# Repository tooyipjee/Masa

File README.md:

**Masa: A Smart, Energy-Efficient Retro Clock**
=====================================================
**Introduction**
---------------
Masa, the Malaysian word for time, is a project that brings together modern electronic components to achieve a beautiful vintage look. Masa combines the aesthetic of traditional Nixie tubes with modern LED technology and advanced features.

**Project Overview**
--------------------
Masa is a type of electronic clock that replicates the vintage aesthetic of traditional Nixie clocks while using modern LED technology. It displays the time and can also display additional panels such as weather, tickers, and other illustrations. Masa has internet connectivity, allowing it to retrieve data from the internet and features several onboard environmental sensors.

**Key Features**
----------------
* LEDs with full brightness and color control
* Environmental sensor to measure room temperature and humidity
* Phototransistor for ambient light measurement
* ESP32-S2 to drive and interface with sensors and get the latest time from the NTP server over WiFi
* Compatible with rapidly prototype-able Cricut-based perspex "displays"
* Powered by USB-C

**Specification**
---------------
* Microcontroller: ESP32-S2
* WiFi: 802.11b/g/n
* FLASH: 4MB
* Programming: USB over UART
* Humidity and Temperature Sensor: SHT20
    + Capacitive type humidity sensor
    + Band gap temperature sensor
    + Digital processing unit - I2C
* Light Sensor: TEMT6000X01
    + High photo sensitivity
    + Adapted to human eye responsivity
    + Angle of half sensitivity ± 60°
* Power: USB-C + 3.3V LDO

**Acknowledgement**
----------------
Special thanks to JLCPCB for sponsoring this project. Their rapid prototyping and high-quality assembly services enabled us to bring this project to life.

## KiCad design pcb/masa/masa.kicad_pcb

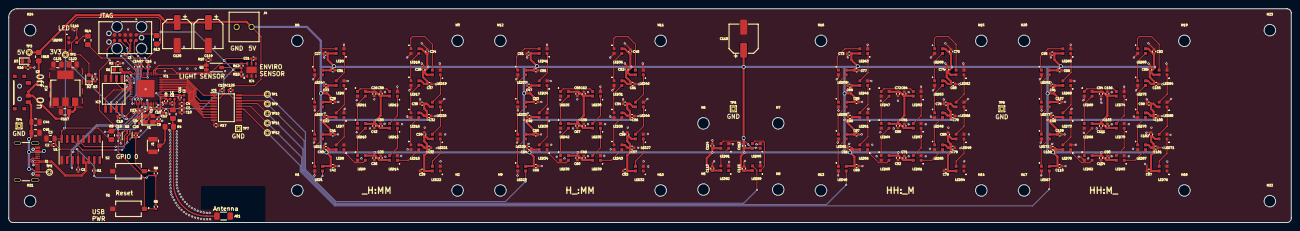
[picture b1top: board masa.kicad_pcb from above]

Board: 4 copper layers, 300.0 x 50.0 mm, 292 parts (0 on the bottom side), 144 nets.

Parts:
AE1: ANT3216LL00R2400A; R_1206_3216Metric_Pad1.30x1.75mm_HandSolder
C1, C2, C10, C13, C15, C16, C17, C18, C21, C22, C23, C24, C25, C26, C27, C28, C29, C30, C31, C32, C33, C34, C35, C36, C37, C38, C39, C40, C41, C42, C43, C46, C47, C48, C49, C50, C51, C52, C53, C54, C55, C56, C57, C58, C59, C60, C61, C62, C63, C64, C65, C66, C67, C68, C69, C70, C71, C72, C73, C74, C75, C76, C77, C78, C79, C80, C81, C82, C83, C84, C85, C86, C87, C88, C89, C90, C91, C92, C93, C94, C95, C96, C97, C98, C99, C100, C101, C102, C103, C104, C105, C106, C107, C108, C109, C110, C111, C112, C113, C114, C115, C116, C124, C125: 100n; C_0402_1005Metric
C3, C44, C45, C117, C121, C122: 10u; C_0805_2012Metric
C4, C12, C19, C20: 1u; C_0402_1005Metric
C5, C9: 20p; C_0402_1005Metric
C6: 4p; C_0402_1005Metric
C7, C11: 10u_0402; C_0402_1005Metric
C8: 5p; C_0402_1005Metric
C14: 100p; C_0402_1005Metric
C118, C119, C120: 100uF_E; CP_Elec_6.3x7.7
D1, D2, D3: Green_0603; LED_0603_1608Metric
H1, H2, H3, H4, H5, H6, H7, H8, H9, H10, H11, H12, H13, H14, H15, H16, H17, H18, H19, H20, H21, H22, H23, H24: MountingHole; MountingHole_2.7mm_M2.5
IC1: ESP32-S2FH4; QFN40P700X700X90-57N-D
IC2: AMS1117-3.3; SOT-223-3_TabPin2
IC3: W25Q64JVSSIQ; SOIC127P790X216-8N
IC4: SHT20; SON100P300X300X110-7N
IC5: TXS0108EPWR; SOP65P640X120-20N
J1: U.FL-R-SMT-1_10_
J2: GT-USB-7010; GT-USB-7010A
J3: TC2050-IDC
J4: KF350-3.5-2P; KF350352P
L1, L2: 1.8nH; L_0402_1005Metric
LED1, LED2, LED3, LED4, LED5, LED6, LED7, LED8, LED9, LED10, LED11, LED12, LED13, LED14, LED15, LED16, LED17, LED18, LED19, LED20, LED21, LED22, LED23, LED24, LED25, LED26, LED27, LED28, LED29, LED30, LED31, LED32, LED33, LED34, LED35, LED36, LED37, LED38, LED39, LED40, LED41, LED42, LED43, LED44, LED45, LED46, LED47, LED48, LED49, LED50, LED51, LED52, LED53, LED54, LED55, LED56, LED57, LED58, LED59, LED60, LED61, LED62, LED63, LED64, LED65, LED66, LED67, LED68, LED69, LED70, LED71, LED72, LED73, LED74, LED75, LED76, LED77, LED78, LED79, LED80, LED81, LED82, LED83, LED84, LED85, LED86, LED87, LED88, LED89, LED90, LED91, LED92, LED93: WS2812B-2020; WS2812B2020
Q1: MUN5214DW1T1G; SOT-363_SC-70-6
Q2: TEMT6000X01
R1: DNF_0402; R_0402_1005Metric
R2, R3: 1k; R_0402_1005Metric
R4, R9, R13: DNF_0805; R_0805_2012Metric_Pad1.20x1.40mm_HandSolder
R5, R14, R15: 0; R_0805_2012Metric_Pad1.20x1.40mm_HandSolder
R6, R7, R8, R10, R17: 10k; R_0402_1005Metric
R11, R12: 4.7k; R_0402_1005Metric
R16: 2.2k; R_0402_1005Metric
S1, S2: TS-1101-C-W; TS1101CW
S3: K3-1296S-E1; K31296SE1
TP1, TP2, TP3, TP5, TP9, TP10, TP11, TP12: TestPoint; TestPoint_THTPad_D1.0mm_Drill0.5mm
TP4, TP6, TP7, TP8: TestPoint; TestPoint_THTPad_1.0x1.0mm_Drill0.5mm
U1: CH340C; SOIC-16_3.9x9.9mm_P1.27mm
Y1: SX25Y040000BF1T-C; Crystal_SMD_2520-4Pin_2.5x2.0mm

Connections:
+3V3: C1.1, C2.1, C3.1, C4.1, C7.1, C10.1, C12.1, C13.1, C14.1, C15.1, C16.1, C17.1, C21.1, C116.1, C121.1, C122.1, C124.1, D2.2 (A), IC1.1 (VDDA_1), IC1.20 (VDD3P3_RTC), IC1.27 (VDD3P3_RTC_IO), IC1.45 (VDD3P3_CPU), IC1.51 (VDDA_2), IC1.54 (VDDA_3), IC2.2 (VO), IC4.5 (VDD), IC5.2 (VCCA), L2.1, LED93.4 (VDD), Q2.3 (C), R1.2, R6.1, R7.1, R8.1, R9.1, R11.1, R12.1, R13.2, TP2.1, U1.4 (V3), U1.16 (VCC)
+5V: C22.1, C23.1, C24.1, C25.1, C26.1, C27.1, C28.1, C29.1, C30.1, C31.1, C32.1, C33.1, C34.1, C35.1, C36.1, C37.1, C38.1, C39.1, C40.1, C41.1, C42.1, C43.1, C46.1, C47.1, C48.1, C49.1, C50.1, C51.1, C52.1, C53.1, C54.1, C55.1, C56.1, C57.1, C58.1, C59.1, C60.1, C61.1, C62.1, C63.1, C64.1, C65.1, C66.1, C67.1, C68.1, C69.1, C70.1, C71.1, C72.1, C73.1, C74.1, C75.1, C76.1, C77.1, C78.1, C79.1, C80.1, C81.1, C82.1, C83.1, C84.1, C85.1, C86.1, C87.1, C88.1, C89.1, C90.1, C91.1, C92.1, C93.1, C94.1, C95.1, C96.1, C97.1, C98.1, C99.1, C100.1, C101.1, C102.1, C103.1, C104.1, C105.1, C106.1, C107.1, C108.1, C109.1, C110.1, C111.1, C112.1, C113.1, C114.1, C115.1, C118.1, C119.1, C120.1, C125.1, D3.2 (A), IC5.19 (VCCB), J4.1, LED1.4 (VDD), LED2.4 (VDD), LED3.4 (VDD), LED4.4 (VDD), LED5.4 (VDD), LED6.4 (VDD), LED7.4 (VDD), LED8.4 (VDD), LED9.4 (VDD), LED10.4 (VDD), LED11.4 (VDD), LED12.4 (VDD), LED13.4 (VDD), LED14.4 (VDD), LED15.4 (VDD), LED16.4 (VDD), LED17.4 (VDD), LED18.4 (VDD), LED19.4 (VDD), LED20.4 (VDD), LED21.4 (VDD), LED22.4 (VDD), LED23.4 (VDD), LED24.4 (VDD), LED25.4 (VDD), LED26.4 (VDD), LED27.4 (VDD), LED28.4 (VDD), LED29.4 (VDD), LED30.4 (VDD), LED31.4 (VDD), LED32.4 (VDD), LED33.4 (VDD), LED34.4 (VDD), LED35.4 (VDD), LED36.4 (VDD), LED37.4 (VDD), LED38.4 (VDD), LED39.4 (VDD), LED40.4 (VDD), LED41.4 (VDD), LED42.4 (VDD), LED43.4 (VDD), LED44.4 (VDD), LED45.4 (VDD), LED46.4 (VDD), LED47.4 (VDD), LED48.4 (VDD), LED49.4 (VDD), LED50.4 (VDD), LED51.4 (VDD), LED52.4 (VDD), LED53.4 (VDD), LED54.4 (VDD), LED55.4 (VDD), LED56.4 (VDD), LED57.4 (VDD), LED58.4 (VDD), LED59.4 (VDD), LED60.4 (VDD), LED61.4 (VDD), LED62.4 (VDD), LED63.4 (VDD), LED64.4 (VDD), LED65.4 (VDD), LED66.4 (VDD), LED67.4 (VDD), LED68.4 (VDD), LED69.4 (VDD), LED70.4 (VDD), LED71.4 (VDD), LED72.4 (VDD), LED73.4 (VDD), LED74.4 (VDD), LED75.4 (VDD), LED76.4 (VDD), LED77.4 (VDD), LED78.4 (VDD), LED79.4 (VDD), LED80.4 (VDD), LED81.4 (VDD), LED82.4 (VDD), LED83.4 (VDD), LED84.4 (VDD), LED85.4 (VDD), LED86.4 (VDD), LED87.4 (VDD), LED88.4 (VDD), LED89.4 (VDD), LED90.4 (VDD), LED91.4 (VDD), LED92.4 (VDD), R15.2, TP3.1
/Connectors/CHIP_PU: C19.1, IC1.56 (CHIP_PU), J3.10 (~RESET), Q1.6 (C2), R6.2, S1.1
/Connectors/MTCK: IC1.43 (MTCK), J3.4 (SWDCLK/TCK)
/Connectors/MTDI: IC1.46 (MTDI), J3.8 (NC/TDI)
/Connectors/MTDO: IC1.44 (MTD0), J3.6 (SWO/TDO)
/Connectors/MTMS: IC1.47 (MTMS), J3.2 (SWDIO/TMS)
/Connectors/USBDN: J2.A7 (D-), J2.B7 (D-), U1.6 (UD-)
/Connectors/USBDP: J2.A6 (D+), J2.B6 (D+), U1.5 (UD+)
/Connectors/VBUS: C117.1, IC2.3 (VI), R15.1, S3.2 (B)
/LED_Array_1/SIG_IN: IC5.20 (B1), LED1.3 (DI), TP1.1
/LED_Array_2/SIG_IN: IC5.18 (B2), LED23.3 (DI), TP9.1
/LED_Array_3/SIG_IN: IC5.16 (B4), LED45.3 (DI), TP11.1
/LED_Array_4/SIG_IN: IC5.15 (B5), LED67.3 (DI), TP12.1
/LED_Array_Small_1/SIG_IN: IC5.17 (B3), LED89.3 (DI), TP10.1
/Level Shifter/A1: IC1.13 (GPIO8), IC5.1 (A1)
/Level Shifter/A2: IC1.12 (GPIO7), IC5.3 (A2)
/Level Shifter/A3: IC1.11 (GPIO6), IC5.4 (A3)
/Level Shifter/A4: IC1.10 (GPIO5), IC5.5 (A4)
/Level Shifter/A5: IC1.9 (GPIO4), IC5.6 (A5)
/Level Shifter/A6: IC1.8 (GPIO3), IC5.7 (A6)
/Level Shifter/A7: IC1.7 (GPIO2), IC5.8 (A7)
/Level Shifter/A8: IC1.6 (GPIO1), IC5.9 (A8)
/Microcontroller/LIGHT_SIG: IC1.17 (GPIO12), Q2.1 (E), Q2.2 (E), R10.1
/Microcontroller/SCL: IC1.16 (GPIO11), IC4.6 (SCL), R12.2
/Microcontroller/SDA: IC1.15 (GPIO10), IC4.1 (SDA), R11.2
/Microcontroller/U0RXD: IC1.49 (U0RXD), U1.2 (TXD)
/Microcontroller/U0TXD: IC1.48 (U0TXD), U1.3 (RXD)
DTR: Q1.2 (B2), Q1.4 (E1), U1.13 (~DTR)
GND: C1.2, C2.2, C3.2, C4.2, C5.2, C6.2, C7.2, C8.2, C9.1, C10.2, C11.2, C12.2, C13.2, C14.2, C15.2, C16.2, C17.2, C18.2, C19.2, C20.2, C21.2, C22.2, C23.2, C24.2, C25.2, C26.2, C27.2, C28.2, C29.2, C30.2, C31.2, C32.2, C33.2, C34.2, C35.2, C36.2, C37.2, C38.2, C39.2, C40.2, C41.2, C42.2, C43.2, C44.2, C45.2, C46.2, C47.2, C48.2, C49.2, C50.2, C51.2, C52.2, C53.2, C54.2, C55.2, C56.2, C57.2, C58.2, C59.2, C60.2, C61.2, C62.2, C63.2, C64.2, C65.2, C66.2, C67.2, C68.2, C69.2, C70.2, C71.2, C72.2, C73.2, C74.2, C75.2, C76.2, C77.2, C78.2, C79.2, C80.2, C81.2, C82.2, C83.2, C84.2, C85.2, C86.2, C87.2, C88.2, C89.2, C90.2, C91.2, C92.2, C93.2, C94.2, C95.2, C96.2, C97.2, C98.2, C99.2, C100.2, C101.2, C102.2, C103.2, C104.2, C105.2, C106.2, C107.2, C108.2, C109.2, C110.2, C111.2, C112.2, C113.2, C114.2, C115.2, C116.2, C117.2, C118.2, C119.2, C120.2, C121.2, C122.2, C124.2, C125.2, IC1.57 (GND), IC2.1 (GND), IC3.4 (GND), IC4.2 (VSS), IC4.7 (EP), IC5.11 (GND), J1.1 (Ext), J1.2 (Ext), J2.A1 (GND), J2.B1 (GND), J3.3 (GND), J3.5 (GND), J3.9 (GNDDetect), J4.2, LED1.2 (GND), LED2.2 (GND), LED3.2 (GND), LED4.2 (GND), LED5.2 (GND), LED6.2 (GND), LED7.2 (GND), LED8.2 (GND), LED9.2 (GND), LED10.2 (GND), LED11.2 (GND), LED12.2 (GND), LED13.2 (GND), LED14.2 (GND), LED15.2 (GND), LED16.2 (GND), LED17.2 (GND), LED18.2 (GND), LED19.2 (GND), LED20.2 (GND), LED21.2 (GND), LED22.2 (GND), LED23.2 (GND), LED24.2 (GND), LED25.2 (GND), LED26.2 (GND), LED27.2 (GND), LED28.2 (GND), LED29.2 (GND), LED30.2 (GND), LED31.2 (GND), LED32.2 (GND), LED33.2 (GND), LED34.2 (GND), LED35.2 (GND), LED36.2 (GND), LED37.2 (GND), LED38.2 (GND), LED39.2 (GND), LED40.2 (GND), LED41.2 (GND), LED42.2 (GND), LED43.2 (GND), LED44.2 (GND), LED45.2 (GND), LED46.2 (GND), LED47.2 (GND), LED48.2 (GND), LED49.2 (GND), LED50.2 (GND), LED51.2 (GND), LED52.2 (GND), LED53.2 (GND), LED54.2 (GND), LED55.2 (GND), LED56.2 (GND), LED57.2 (GND), LED58.2 (GND), LED59.2 (GND), LED60.2 (GND), LED61.2 (GND), LED62.2 (GND), LED63.2 (GND), LED64.2 (GND), LED65.2 (GND), LED66.2 (GND), LED67.2 (GND), LED68.2 (GND), LED69.2 (GND), LED70.2 (GND), LED71.2 (GND), LED72.2 (GND), LED73.2 (GND), LED74.2 (GND), LED75.2 (GND), LED76.2 (GND), LED77.2 (GND), LED78.2 (GND), LED79.2 (GND), LED80.2 (GND), LED81.2 (GND), LED82.2 (GND), LED83.2 (GND), LED84.2 (GND), LED85.2 (GND), LED86.2 (GND), LED87.2 (GND), LED88.2 (GND), LED89.2 (GND), LED90.2 (GND), LED91.2 (GND), LED92.2 (GND), LED93.2 (GND), R2.2, R3.2, R10.2, R16.2, R17.1, S1.2, S2.2, TP4.1, TP6.1, TP7.1, TP8.1, U1.1 (GND), Y1.2, Y1.4
GPIO0: C20.1, IC1.5 (GPIO0), Q1.3 (C1), R8.2, S2.1
GPIO18: IC1.24 (DAC_2), R7.2, R14.1
GPIO45: IC1.50 (GPIO45), R9.2
unnamed: AE1.2 (PCB_Trace), R4.2, R5.2
unnamed: C5.1, IC1.52 (XTAL_N), Y1.1
unnamed: C6.1, L1.1, R5.1
unnamed: C8.1, IC1.2 (LNA_IN), L1.2
unnamed: C9.2, IC1.53 (XTAL_P), Y1.3
unnamed: C11.1, IC1.3 (VDD3P3_1), IC1.4 (VDD3P3_2), L2.2
unnamed: C44.1, C45.1, J2.A4 (VBUS), J2.A9 (VBUS), J2.B4 (VBUS), J2.B9 (VBUS), S3.1 (A), TP5.1
unnamed: D1.1 (K), R2.1
unnamed: D1.2 (A), IC1.28 (GPIO21)
unnamed: D2.1 (K), R3.1
unnamed: D3.1 (K), R16.1
unnamed: IC5.10 (OE), R17.2
unnamed: J1.3 (In), R4.1
unnamed: J3.1 (VTref), R13.1
unnamed: LED1.1 (DO), LED2.3 (DI)
unnamed: LED2.1 (DO), LED3.3 (DI)
unnamed: LED3.1 (DO), LED4.3 (DI)
unnamed: LED4.1 (DO), LED5.3 (DI)
unnamed: LED5.1 (DO), LED6.3 (DI)
unnamed: LED6.1 (DO), LED7.3 (DI)
unnamed: LED7.1 (DO), LED8.3 (DI)
unnamed: LED8.1 (DO), LED9.3 (DI)
unnamed: LED10.1 (DO), LED11.3 (DI)
unnamed: LED9.1 (DO), LED10.3 (DI)
unnamed: LED11.1 (DO), LED12.3 (DI)
unnamed: LED12.1 (DO), LED13.3 (DI)
unnamed: LED13.1 (DO), LED14.3 (DI)
unnamed: LED14.1 (DO), LED15.3 (DI)
unnamed: LED15.1 (DO), LED16.3 (DI)
unnamed: LED16.1 (DO), LED17.3 (DI)
unnamed: LED17.1 (DO), LED18.3 (DI)
unnamed: LED18.1 (DO), LED19.3 (DI)
unnamed: LED19.1 (DO), LED20.3 (DI)
unnamed: LED20.1 (DO), LED21.3 (DI)
unnamed: LED21.1 (DO), LED22.3 (DI)
unnamed: LED23.1 (DO), LED28.3 (DI)
unnamed: LED24.1 (DO), LED29.3 (DI)
unnamed: LED24.3 (DI), LED41.1 (DO)
unnamed: LED25.1 (DO), LED30.3 (DI)
unnamed: LED25.3 (DI), LED42.1 (DO)
unnamed: LED26.1 (DO), LED31.3 (DI)
unnamed: LED26.3 (DI), LED43.1 (DO)
unnamed: LED27.1 (DO), LED32.3 (DI)
unnamed: LED27.3 (DI), LED44.1 (DO)
unnamed: LED28.1 (DO), LED33.3 (DI)
unnamed: LED29.1 (DO), LED34.3 (DI)
unnamed: LED30.1 (DO), LED35.3 (DI)
unnamed: LED31.1 (DO), LED36.3 (DI)
unnamed: LED33.1 (DO), LED37.3 (DI)
unnamed: LED34.1 (DO), LED38.3 (DI)
unnamed: LED35.1 (DO), LED39.3 (DI)
unnamed: LED36.1 (DO), LED40.3 (DI)
unnamed: LED37.1 (DO), LED41.3 (DI)
unnamed: LED38.1 (DO), LED42.3 (DI)
unnamed: LED39.1 (DO), LED43.3 (DI)
unnamed: LED40.1 (DO), LED44.3 (DI)
unnamed: LED45.1 (DO), LED50.3 (DI)
unnamed: LED46.1 (DO), LED51.3 (DI)
unnamed: LED46.3 (DI), LED63.1 (DO)
unnamed: LED47.1 (DO), LED52.3 (DI)
unnamed: LED47.3 (DI), LED64.1 (DO)
unnamed: LED48.1 (DO), LED53.3 (DI)
unnamed: LED48.3 (DI), LED65.1 (DO)
unnamed: LED49.1 (DO), LED54.3 (DI)
unnamed: LED49.3 (DI), LED66.1 (DO)
unnamed: LED50.1 (DO), LED55.3 (DI)
unnamed: LED51.1 (DO), LED56.3 (DI)
unnamed: LED52.1 (DO), LED57.3 (DI)
unnamed: LED53.1 (DO), LED58.3 (DI)
unnamed: LED55.1 (DO), LED59.3 (DI)
unnamed: LED56.1 (DO), LED60.3 (DI)
unnamed: LED57.1 (DO), LED61.3 (DI)
unnamed: LED58.1 (DO), LED62.3 (DI)
unnamed: LED59.1 (DO), LED63.3 (DI)
unnamed: LED60.1 (DO), LED64.3 (DI)
unnamed: LED61.1 (DO), LED65.3 (DI)
unnamed: LED62.1 (DO), LED66.3 (DI)
unnamed: LED67.1 (DO), LED72.3 (DI)
unnamed: LED68.1 (DO), LED73.3 (DI)
unnamed: LED68.3 (DI), LED85.1 (DO)
unnamed: LED69.1 (DO), LED74.3 (DI)
unnamed: LED69.3 (DI), LED86.1 (DO)
unnamed: LED70.1 (DO), LED75.3 (DI)
unnamed: LED70.3 (DI), LED87.1 (DO)
unnamed: LED71.1 (DO), LED76.3 (DI)
unnamed: LED71.3 (DI), LED88.1 (DO)
unnamed: LED72.1 (DO), LED77.3 (DI)
unnamed: LED73.1 (DO), LED78.3 (DI)
unnamed: LED74.1 (DO), LED79.3 (DI)
unnamed: LED75.1 (DO), LED80.3 (DI)
unnamed: LED77.1 (DO), LED81.3 (DI)
unnamed: LED78.1 (DO), LED82.3 (DI)
unnamed: LED79.1 (DO), LED83.3 (DI)
unnamed: LED80.1 (DO), LED84.3 (DI)
unnamed: LED81.1 (DO), LED85.3 (DI)
unnamed: LED82.1 (DO), LED86.3 (DI)
unnamed: LED83.1 (DO), LED87.3 (DI)
unnamed: LED84.1 (DO), LED88.3 (DI)
unnamed: LED89.1 (DO), LED90.3 (DI)
unnamed: LED90.1 (DO), LED91.3 (DI)
unnamed: LED91.1 (DO), LED92.3 (DI)
unnamed: LED93.3 (DI), R14.2
unnamed: R1.1, U1.7 (~RST)
RTS: Q1.1 (E2), Q1.5 (B1), U1.14 (~RTS)
SPICLK: IC1.34 (SPICLK), IC3.6 (CLK)
SPICS0: IC1.33 (SPICS0), IC3.1 (~CS)
SPID: IC1.36 (SPID), IC3.5 (DI(IO0))
SPIHD: IC1.31 (SPIHD), IC3.7 (IO3)
SPIQ: IC1.35 (SPIQ), IC3.2 (DO(IO1))
SPIWP: IC1.32 (SPIWP), IC3.3 (IO2)
VDD_SPI: C18.1, IC1.30 (VDD_SPI), IC3.8 (VCC)

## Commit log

2023-01-22 created test script
2023-01-23 fixed bug and added increasing brightness into loop
2023-04-22 Written software
2023-04-23 Updated with OTA and WiFiManager
2023-04-24 added parameter
2023-04-24 Added weather param
2023-04-24 Added debug telnet stream
2023-04-24 Fixed bug with storing weather location
